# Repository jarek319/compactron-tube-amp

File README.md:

# compactron-tube-amp
All-in-one amp using an all-in-one tube!

Very much a work in progress.

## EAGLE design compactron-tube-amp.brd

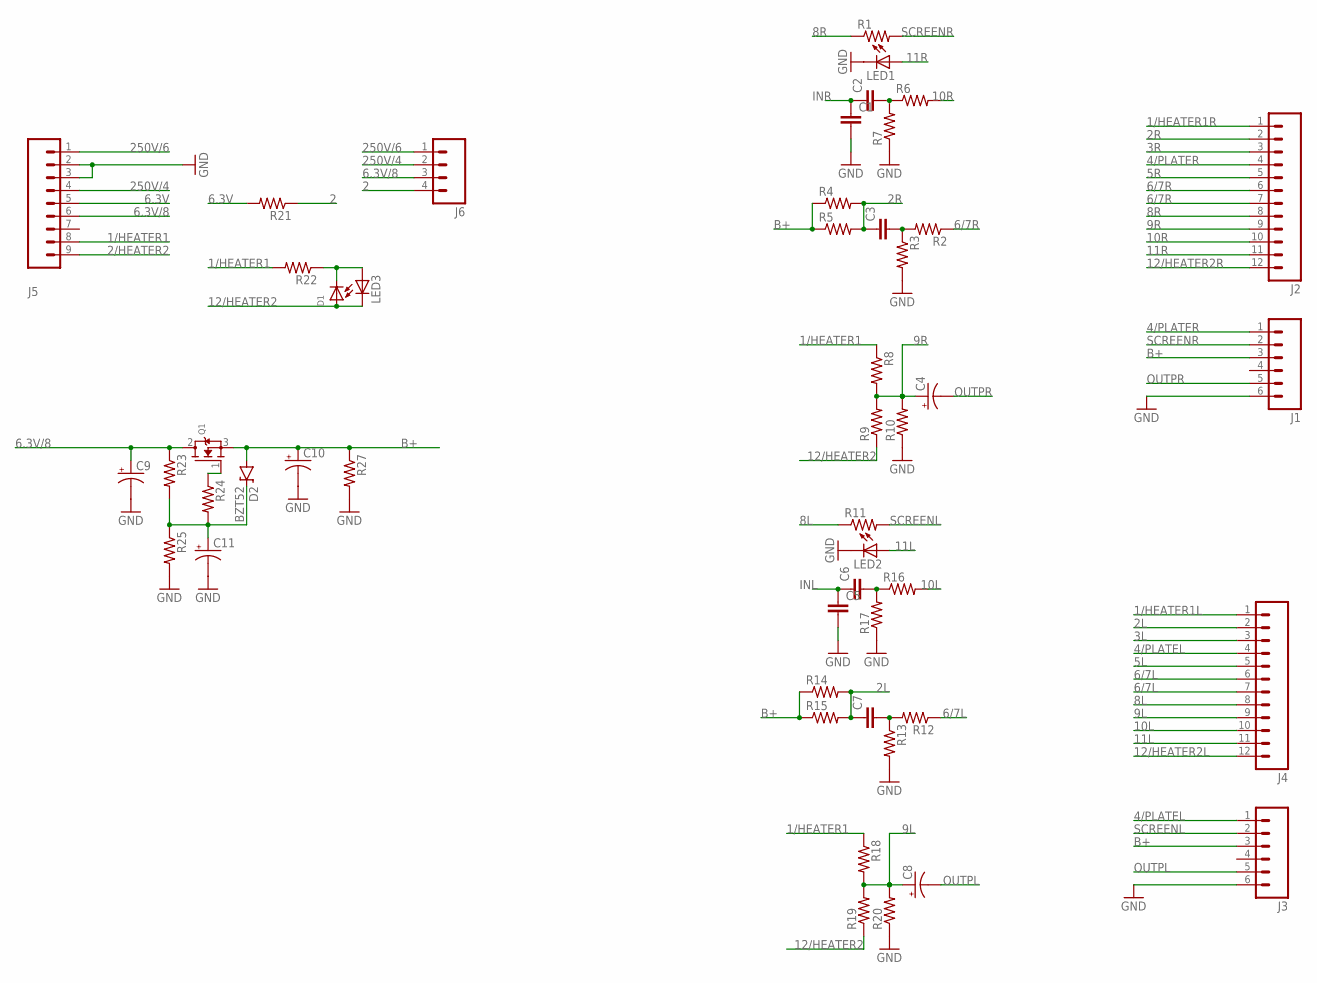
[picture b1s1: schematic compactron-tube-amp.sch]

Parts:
C1, C2, C3, C5, C6, C7: C-EU275-093X316; C275-093X316
C4, C8, C9, C10, C11: CPOL-USE22-10AXIAL; E22-10
D1: DIODEDO-1N4148; DO-1N4148
D2: BZT52; DIODE-BZT52
J1, J3: M06LONGPADS; 1X06_LONGPADS
J2, J4: M12LONGPADS; 1X12_LONGPADS
J5: M09LONGPADS; 1X09_LONGPADS
J6: M04LONGPADS; 1X04_LONGPADS
LED1, LED2, LED3: LED5MM
Q1: MOSFET-NGDS_TO220V; TO220V
R1, R2, R3, R4, R5, R6, R7, R8, R9, R10, R11, R12, R13, R14, R15, R16, R17, R18, R19, R20, R21, R22, R23, R24, R25, R27: RESISTORPTH-2W; AXIAL-0.8

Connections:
1/HEATER1: J5.8, R8.P$1 (1), R18.P$1 (1), R22.P$2 (2)
1/HEATER1L: J4.1
1/HEATER1R: J2.1
2: J6.4, R21.P$1 (1)
2/HEATER2: J5.9
2L: C7.1, J4.2, R14.P$2 (2), R15.P$2 (2)
2R: C3.1, J2.2, R4.P$2 (2), R5.P$2 (2)
3L: J4.3
3R: J2.3
4/PLATEL: J3.1, J4.4
4/PLATER: J1.1, J2.4
5L: J4.5
5R: J2.5
6.3V: J5.5, R21.P$2 (2)
6.3V/8: C9.+, J5.6, J6.3, Q1.2 (D), R23.P$1 (1)
6/7L: J4.6, J4.7, R12.P$1 (1)
6/7R: J2.6, J2.7, R2.P$1 (1)
8L: J4.8, R11.P$1 (1)
8R: J2.8, R1.P$1 (1)
9L: C8.+, J4.9, R18.P$2 (2), R19.P$2 (2), R20.P$2 (2)
9R: C4.+, J2.9, R8.P$2 (2), R9.P$2 (2), R10.P$2 (2)
10L: J4.10, R16.P$2 (2)
10R: J2.10, R6.P$2 (2)
11L: J4.11, LED2.A
11R: J2.11, LED1.A
12/HEATER2: D1.A, LED3.K (C), R9.P$1 (1), R19.P$1 (1)
12/HEATER2L: J4.12
12/HEATER2R: J2.12
250V/4: J5.4, J6.2
250V/6: J5.1, J6.1
B+: C10.+, D2.A, J1.3, J3.3, Q1.3 (S), R4.P$1 (1), R5.P$1 (1), R14.P$1 (1), R15.P$1 (1), R27.P$1 (1)
GND: C1.2, C5.2, C9.-, C10.-, C11.-, J1.6, J3.6, J5.2, J5.3, LED1.K (C), LED2.K (C), R3.P$2 (2), R7.P$1 (1), R10.P$1 (1), R13.P$2 (2), R17.P$1 (1), R20.P$1 (1), R25.P$2 (2), R27.P$2 (2)
INL: C5.1, C6.1
INR: C1.1, C2.1
unnamed: C7.2, R12.P$2 (2), R13.P$1 (1)
unnamed: C6.2, R16.P$1 (1), R17.P$2 (2)
unnamed: D1.C, LED3.A, R22.P$1 (1)
unnamed: Q1.1 (G), R24.P$1 (1)
unnamed: C3.2, R2.P$2 (2), R3.P$1 (1)
unnamed: C11.+, D2.C, R23.P$2 (2), R24.P$2 (2), R25.P$1 (1)
unnamed: C2.2, R6.P$1 (1), R7.P$2 (2)
OUTPL: C8.-, J3.5
OUTPR: C4.-, J1.5
SCREENL: J3.2, R11.P$2 (2)
SCREENR: J1.2, R1.P$2 (2)

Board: 2 copper layers, 49 parts (0 on the bottom side), 36 nets, no tracks yet.

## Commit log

2018-07-05 Work in progress

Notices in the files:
parts and their libraries:
SparkFun-Connectors: Licensing: Creative Commons ShareAlike 4.0 International - https://creativecommons.org/licenses/by-sa/4.0
